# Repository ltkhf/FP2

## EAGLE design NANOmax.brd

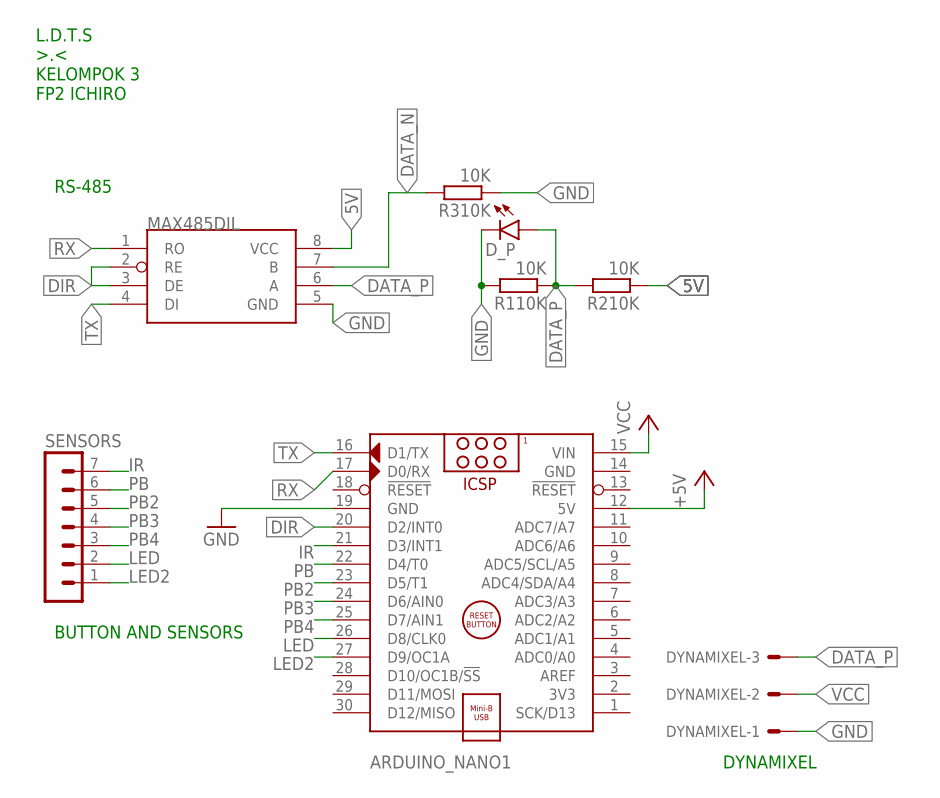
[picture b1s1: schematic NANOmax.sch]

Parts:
ARDUINO_NANO1: ARDUINO_NANO
DYNAMIXEL: 22-27-2031-03; 6410-03
D_P: LED3MM
MAX485: MAX485DIL; DIL08
R110K, R210K, R310K: 10K; 0204/7
SENSORS: MA07-1

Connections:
5V: MAX485.8 (VCC), R210K.1
+5V: ARDUINO_NANO1.12 (5V)
DATA_N: MAX485.7 (B), R310K.2
DATA_P: DYNAMIXEL.3, D_P.A, MAX485.6 (A), R110K.1, R210K.2
DIR: ARDUINO_NANO1.20 (D2/INT0), MAX485.2 (RE), MAX485.3 (DE)
GND: ARDUINO_NANO1.14 (GND), ARDUINO_NANO1.19 (GND), DYNAMIXEL.1, D_P.K (C), MAX485.5 (GND), R110K.2, R310K.1
IR: ARDUINO_NANO1.21 (D3/INT1), SENSORS.7
LED: ARDUINO_NANO1.26 (D8/CLK0), SENSORS.2
LED2: ARDUINO_NANO1.27 (D9/OC1A), SENSORS.1
PB: ARDUINO_NANO1.22 (D4/T0), SENSORS.6
PB2: ARDUINO_NANO1.23 (D5/T1), SENSORS.5
PB3: ARDUINO_NANO1.24 (D6/AIN0), SENSORS.4
PB4: ARDUINO_NANO1.25 (D7/AIN1), SENSORS.3
RX: ARDUINO_NANO1.17 (D0/RX), MAX485.1 (RO)
TX: ARDUINO_NANO1.16 (D1/TX), MAX485.4 (DI)
VCC: ARDUINO_NANO1.15 (VIN), DYNAMIXEL.2

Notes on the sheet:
DYNAMIXEL
RS-485
BUTTON AND SENSORS
L.D.T.S >.< KELOMPOK 3 FP2 ICHIRO

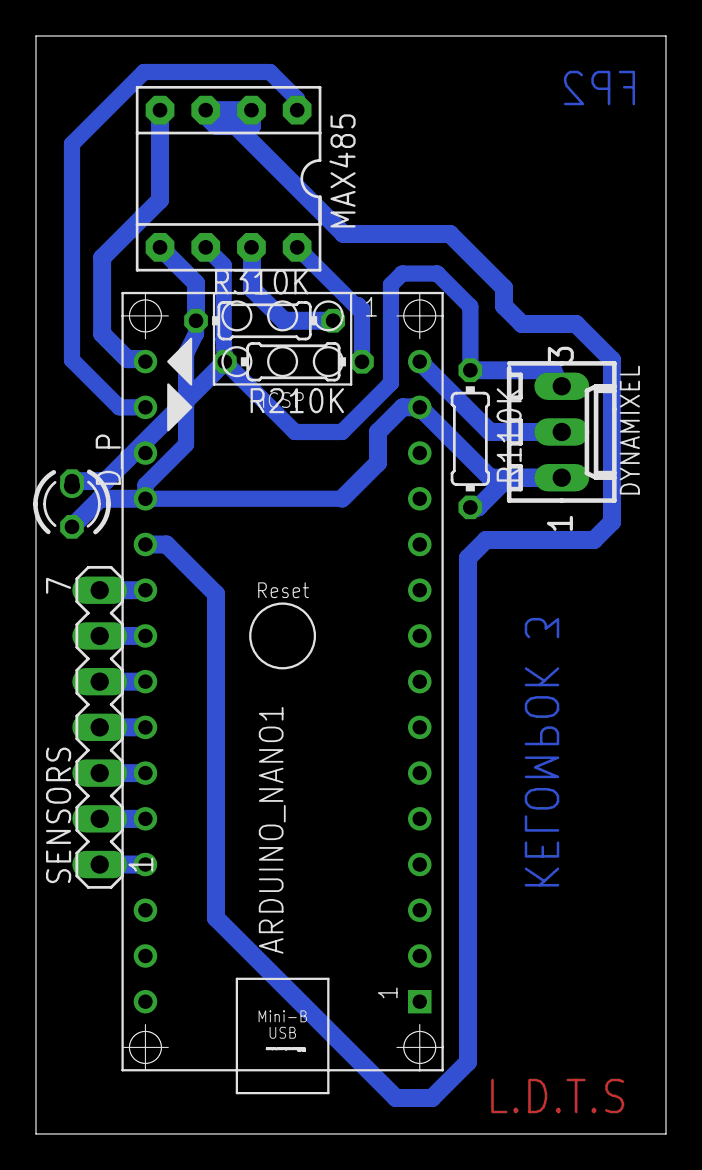
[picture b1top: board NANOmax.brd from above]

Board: 2 copper layers, 35.0 x 61.0 mm, 8 parts (0 on the bottom side), 15 nets.

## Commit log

2022-12-03 Create update
